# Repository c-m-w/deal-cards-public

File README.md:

# Automatic Card Dealer

A robot that deals playing cards to multiple players around a table. A single central motor rotates the whole mechanism to aim at each player in turn, a brushless motor launches the card, and a closed-loop sensor confirms the card actually left before moving on. Everything runs on one ESP32-S3.

This was a project to get hands-on with real-time motion control on a microcontroller: writing a PID controller with a proper trajectory planner from scratch, and driving the ESP32's hardware pulse-counter peripheral directly instead of reaching for a library.

## Demo

Click a thumbnail to play the video (GitHub only plays video on the file's own page, not inline in the README).

*PID driving to a sequence of positions, firing a card at each one, then moving to the next, simulating a full deal around the table. The VCNT2030 proximity sensor gives closed-loop confirmation that a card actually launched before the robot advances, so a jam or misfeed doesn't get treated as a successful deal. This clip is from an earlier hardware revision.*

| | |
|---|---|
|  | **Teleoperation.** Manually driving the central axis with the control box knob. |
|  | **Homing sequence.** Automatic homing against the limit switches on power-up. |
|  | **PID tuning.** Live on-device menu for tuning `K_p`, `K_i`, `K_d`, `K_ff` and driving to a test position, no reflashing required. |
|  | **Belt-drive prototype.** GT2 belt + BLDC + SimpleFOCMini test rig for the next revision of the axis (see [Future work](#future-work)). |

## How it works

The robot is built around one rotating stage (the "central axis") that carries the card deck and launcher. To deal a card, it rotates to a player's angle, spins up the launch motor, and feeds a card into it with a roller; a proximity sensor confirms the card left before the sequence continues.

- **Central axis**: a Pololu gear motor with a quadrature encoder, driving the whole assembly on a lazy-susan bearing. Position is closed-loop via a custom PID controller (see below), or it can be driven open-loop from the control box knob.
- **Launcher**: a drone BLDC motor with an O-ring mounted on a disc, spun up to grip and shoot the card once it's fed into it.
- **Feeder**: a JGY-070 worm gearmotor turning a rod fitted with rollers pulled from a printer, which slowly pushes one card at a time out toward the launcher.
- **Card detection**: a VCNT2030 IR proximity sensor watches the launch point so the firmware knows a card was actually dealt, rather than assuming it based on timing.
- **Homing**: limit switches on both ends of travel let the robot find its zero position and travel limits automatically on startup, with no manual calibration.
- **Control box**: three mechanical-keyboard switches, a 240x320 SPI TFT, and a rotary knob (an AS5600 magnetic encoder under the hood) for menu navigation, manual jogging, and live PID tuning.
- **E-stop**: a physical emergency stop button for cutting the motors.

Everything (motion control, sensor polling, the menu system, and the display) runs on a single ESP32-S3 (Arduino framework, PlatformIO). The display is driven on its own FreeRTOS task pinned to core 0 so redrawing the UI never blocks the control loop.

## Central axis motion control

The central axis needs to land on a target angle accurately and repeatably; dealing to the wrong spot, or overshooting into a player, isn't acceptable. It's driven by a PID controller I wrote for this project ([`pid_controller.cpp`](code-esp32/src/pid_controller.cpp)), not a library, tracking a **quintic (5th-order) polynomial trajectory** rather than chasing the setpoint directly.

**Why a trajectory planner instead of just a setpoint.** Feeding a PID loop a step input (jump straight to the goal angle) begs for overshoot and a jerky start/stop, which is rough on the gearbox and the coupling. Instead, `plan_quintic()` computes a smooth minimum-jerk profile between the start and goal angle: position, velocity, and acceleration are all continuous, and both velocity and acceleration are exactly zero at the endpoints. The move duration is scaled by how far the axis has to travel (`T_ms = max(T_ms_min, |Δangle| / angular_speed)`), so short moves aren't forced to take as long as long ones.

**The control law** combines four terms every cycle:

- **P** on position error (planned position vs. measured encoder angle)
- **I** on accumulated position error, with **anti-windup**: the integral only accumulates while the output isn't saturated, so it can't wind up during a stall or a move that's temporarily maxed out at ±1.0
- **D** on *velocity* error, comparing the planner's target velocity against the measured velocity
- **Feedforward** on the planner's target velocity, so the motor is already being driven at roughly the right speed before the feedback terms have to correct for anything

Velocity isn't read directly off the encoder; it's a finite difference of successive angle readings, smoothed with an exponential low-pass filter (`α = 0.2`) so encoder quantization noise doesn't get amplified into a noisy derivative term and fed back into the motor.

One deliberate departure from textbook PID: once the controller has decided which direction to move, it adds a fixed minimum-speed offset before sending the command to the motor driver. The gear motor has enough static friction that small commanded speeds near zero just stall rather than moving, and a plain PID output tends to hover in that dead zone as it approaches the goal. The minimum-speed kick keeps the motor actually turning through the whole approach, which is what gets the steady-state accuracy down.

The result is final-position accuracy consistently **under 2°**. Because it's an on-device tunable loop rather than baked-in constants, all four gains can be adjusted live from the control box's PID tuning menu (see the demo above) while watching the axis respond in real time, no reflash, no recompiling.

For offline analysis, the firmware also prints structured `>name:series(x,y)` lines over serial for the planned/measured position and velocity each cycle, which [`plot-pid/plot.py`](plot-pid/plot.py) reads and live-plots: an arbitrary number of named plots, each with an arbitrary number of lines, built up automatically from whatever the firmware prints. That's how the gains were actually tuned and how the `<2°` figure was verified.

## Quadrature decoding on the ESP32's PCNT peripheral

The central axis encoder is read entirely in hardware rather than in software. The ESP32-S3 has a dedicated **PCNT (Pulse Counter) peripheral** that can count encoder edges without touching the CPU: no interrupt handler in the hot path, no risk of missing an edge if something else briefly blocks the core.

Rather than a wrapper library, [`axis_control.cpp`](code-esp32/src/axis_control.cpp) configures the PCNT unit directly against `driver/pcnt.h`. Standard single-channel PCNT usage only counts edges on one signal and reads direction off the other, giving 2x decoding. To get full **4x decoding** (counting every edge of both encoder channels A and B), two PCNT channels are configured against the *same* physical pins with the roles swapped:

- **Channel 0**: pulses on A, gated by B, with B's level-control action inverted
- **Channel 1**: pulses on B, gated by A, with A's level-control action inverted

Each channel counts both the rising and falling edge of its own pulse input, and the other line's level (inverted on one channel, kept on the other) determines whether that edge counts up or down. Between the two channels, every edge on every line contributes a count, quadrupling the effective resolution over the raw encoder without any additional hardware. The peripheral's built-in glitch filter is also enabled (`pcnt_set_filter_value(100)`), rejecting short noise pulses on the encoder lines entirely in hardware.

Reading the position is then just a register read (`pcnt_get_counter_value`), converted to degrees using the encoder's counts-per-revolution and the axis's gear reduction:

```cpp
const float gearRatio = 1225.f / 12.f;   // motor shaft turns : output shaft turns
const float angle = (float)count / 64.0f / gearRatio * 360.0f;
```

This hardware-counted, zero-CPU-overhead angle is what both the PID controller and the homing routine read every cycle.

## Homing

On startup the robot doesn't know its position, so it runs a homing sequence before anything else is enabled ([`robot::do_homing()`](code-esp32/src/robot.cpp)):

1. **Direction sanity check**: nudge the motor briefly and confirm the encoder moved in the expected direction, catching a miswired encoder or motor before it can drive into a hard stop the wrong way.
2. **Drive to the negative limit switch**, zero the encoder there.
3. **Drive to the positive limit switch**, ramping down speed as it approaches so it doesn't slam the mechanical stop, and record the encoder count at that end.
4. **Set the usable travel range** from the two measured limits (with a small safety margin inset from each hard stop), then return to the middle of the range as a known starting position.

The travel range recorded here is what `robot::move_to()` and the manual jog controls clamp against afterward, and what the control box's knob position is clamped to as well, so it's not possible to command the axis somewhere it can't physically reach.

## Closed-loop dealing

Dealing a single card ([`robot::fire()`](code-esp32/src/robot.cpp)) spins up the launch BLDC, starts the feeder rollers, and then **waits on the VCNT2030 proximity sensor** rather than a fixed delay before considering the card dealt and moving to the next player. If a card doesn't feed cleanly, the robot waits rather than silently skipping a player.

## VCNT2030 breakout board

The VCNT2030 proximity sensor used for [card detection](#how-it-works) runs on a small breakout board I designed myself (KiCad) and had fabricated through JLCPCB, rather than a stock module. The layout follows the sensor's [application note](vcnt2030-breakout/designing_vcnt2030_into_an_application.pdf) for ambient-light suppression and long-range operation, and includes a decoupling capacitor across the sensor's DC supply pins to keep switching noise from the rest of the board out of the analog front end.

*Schematic and PCB layout for the VCNT2030 breakout board.*

## Control box

The handheld control box talks to the robot's ESP32-S3 over GPIO/I2C and drives a small SPI TFT menu system ([`src/menu`](code-esp32/src/menu)):

- **Rotary knob**: an AS5600 magnetic angle sensor read over I2C, exposing both cumulative position (for menu scrolling / jogging) and angular speed (smoothed over a rolling 20-sample window) for teleoperation.
- **Three switches**: enter/up/down for menu navigation, jogging, and triggering a deal.
- **Screens**: a homing prompt, a live homing-progress display, and the PID tuning screen shown in the demo above.

*Control box CAD, the assembled internals (TFT, switches, AS5600), and a labeled CAD view of the knob/magnet/bearing stack around the AS5600.*

## Hardware overview

*The launcher assembly: central axis motor, feeder, launch BLDC, and card holder. Motor drivers and other electronics live under the top panel.*

| | |
|---|---|
|  | Most recent version of the robot. |
|  | The lazy-susan bearing the whole apparatus rotates on, and the normally-open limit switches used for homing. |
|  | The BLDC launch motor and the VCNT2030 proximity sensor used to detect a dealt card. |
|  | The worm-gear feeder motor and the card holder. |
|  | Feeder rollers repurposed from a printer, and the screws used to adjust card holder height until feeding is reliable. |
|  | Motor drivers and power distribution for the whole robot. |
|  | The coupling between the Pololu motor shaft and the robot's rotating base. |

The card holder's height is adjustable via four screws so the feeder rollers can be tuned to grip reliably across different card stock.

## Code

- [`code-esp32/`](code-esp32): PlatformIO firmware project targeting a Freenove ESP32-S3, Arduino framework.
  - [`src/pid_controller.*`](code-esp32/src/pid_controller.cpp): quintic trajectory planner and the PID+feedforward control loop.
  - [`src/axis_control.*`](code-esp32/src/axis_control.cpp): PWM motor driver, limit switches, and the hardware PCNT quadrature decoding.
  - [`src/robot.*`](code-esp32/src/robot.cpp): homing, `move_to`, and `fire`, the high-level behaviors built on top of `axis_control` and `pid_controller`.
  - [`src/controller.*`](code-esp32/src/controller.cpp): the control box, covering buttons, display, and the AS5600 rotary knob.
  - [`src/components/`](code-esp32/src/components): drivers for the feeder motor, launch motor, and VCNT2030 sensor.
  - [`src/menu/`](code-esp32/src/menu): the TFT menu system and its screens (homing, homing prompt, PID tuning).
- [`plot-pid/`](plot-pid): a Python tool that reads the ESP32's serial output and live-plots any `>plot_name:line_name(x,y)` lines the firmware prints. Any number of plots and lines are picked up automatically; this is what the PID tuning is verified against.
- [`CAD/`](CAD): mechanical design files.
- [`vcnt2030-breakout/`](vcnt2030-breakout): KiCad project for the custom VCNT2030 sensor breakout board.
- [`media/`](media): photos and demo videos.

## Future work

- **Better central axis actuation**: replacing the Pololu gear motor + encoder with a brushless gimbal motor, a [SimpleFOCMini](https://simplefoc.com/) driver, and an AS5600 for direct-drive field-oriented control. This removes gearbox backlash and the encoder-resolution ceiling of the current setup, and opens the door to torque control instead of just position/velocity. The belt-drive test video above is an early prototype of this.
- **Wireless control box**: moving to two ESP32s, one in the control box and one on the robot, communicating over ESP-NOW instead of a cable run between them.

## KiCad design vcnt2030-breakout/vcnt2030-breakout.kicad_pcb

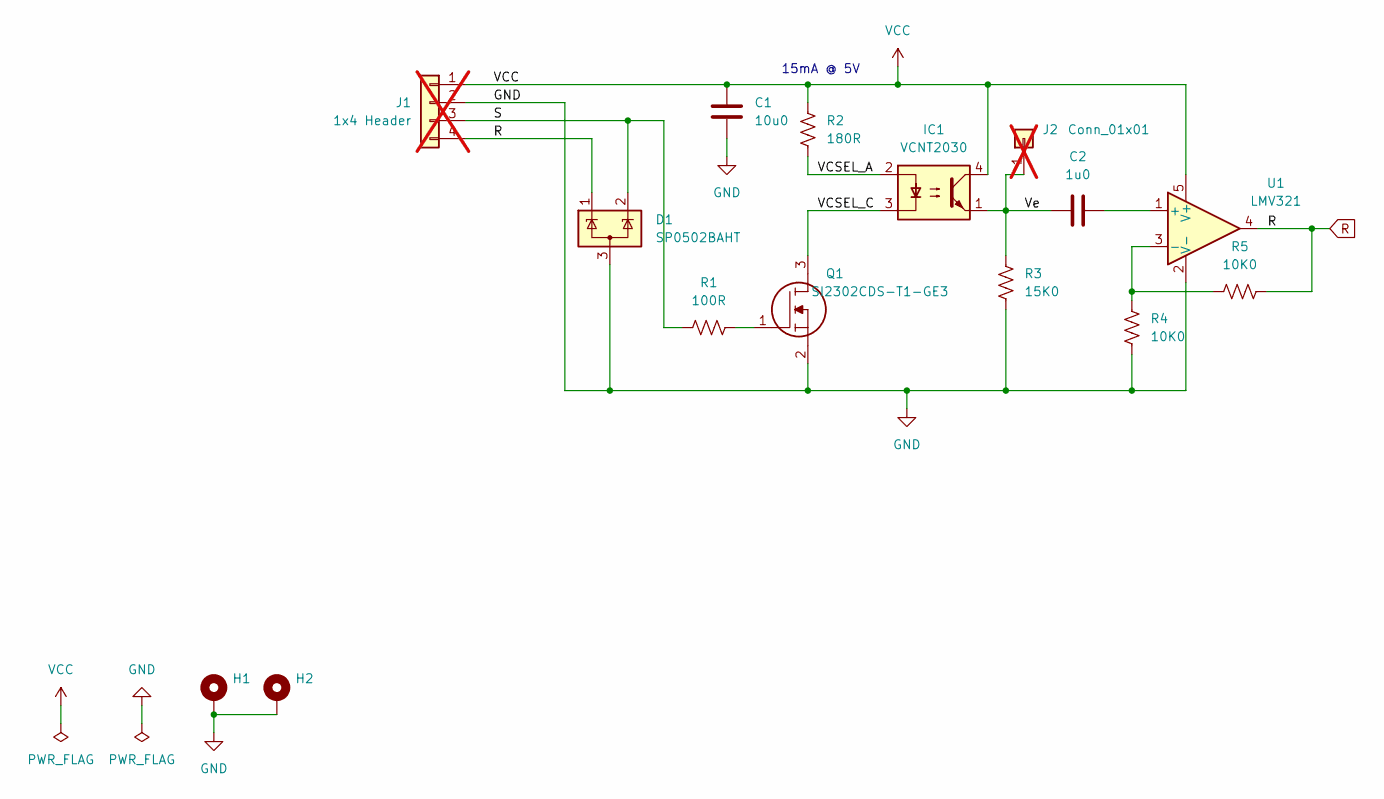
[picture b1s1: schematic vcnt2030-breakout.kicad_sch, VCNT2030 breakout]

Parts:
C1: 10u0; C_0805_2012Metric
C2: 1u0; C_0603_1608Metric
D1: SP0502BAHT; SOT-23
H1, H2: MountingHole_Pad; MountingHole_2.2mm_M2_Pad
IC1: VCNT2030; Manufacturer_Part_Number VCNT2030
J1: 1x4 Header; PinHeader_1x04_P2.54mm_Vertical; not fitted
J2: Conn_01x01; PinHeader_1x01_P2.54mm_Vertical; not fitted
Q1: SI2302CDS-T1-GE3; SOT95P237X112-3N; Mouser Part Number 781-SI2302CDS-T1-GE3
R1: 100R; R_0603_1608Metric
R2: 180R; R_0603_1608Metric
R3: 15K0; R_0603_1608Metric
R4, R5: 10K0; R_0603_1608Metric
U1: LMV321; SOT-23-5

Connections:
/S: D1.2 (K), J1.3, R1.1
/VCSEL_A: IC1.2, R2.2
/VCSEL_C: IC1.3, Q1.3
/Ve: C2.1, IC1.1, J2.1 (Pin_1_1), R3.1
GND: C1.2, D1.3 (A), H1.1 (1_1), H2.1 (1_1), J1.2, Q1.2, R3.2, R4.2, U1.2 (V-)
unnamed: Q1.1, R1.2
unnamed: C2.2, U1.1 (+)
unnamed: R4.1, R5.1, U1.3 (-)
R: D1.1 (K), J1.4, R5.2, U1.4
VCC: C1.1, IC1.4, J1.1, R2.1, U1.5 (V+)

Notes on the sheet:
15mA @ 5V

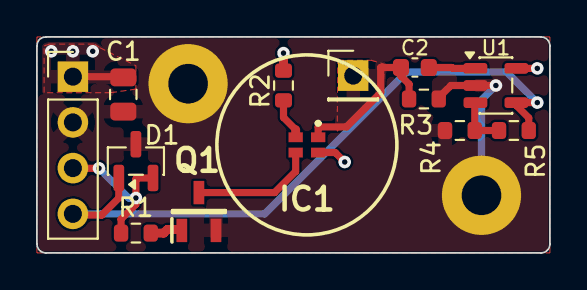
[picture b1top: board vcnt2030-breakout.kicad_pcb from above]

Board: 2 copper layers, 28.5 x 12.0 mm, 15 parts (0 on the bottom side), 10 nets.
